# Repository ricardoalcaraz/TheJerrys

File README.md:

# The Jerrys Micromouse Team
*******************************************
Code for solving 16x16 maze using floodfill algorithm on Tensilica architecture.

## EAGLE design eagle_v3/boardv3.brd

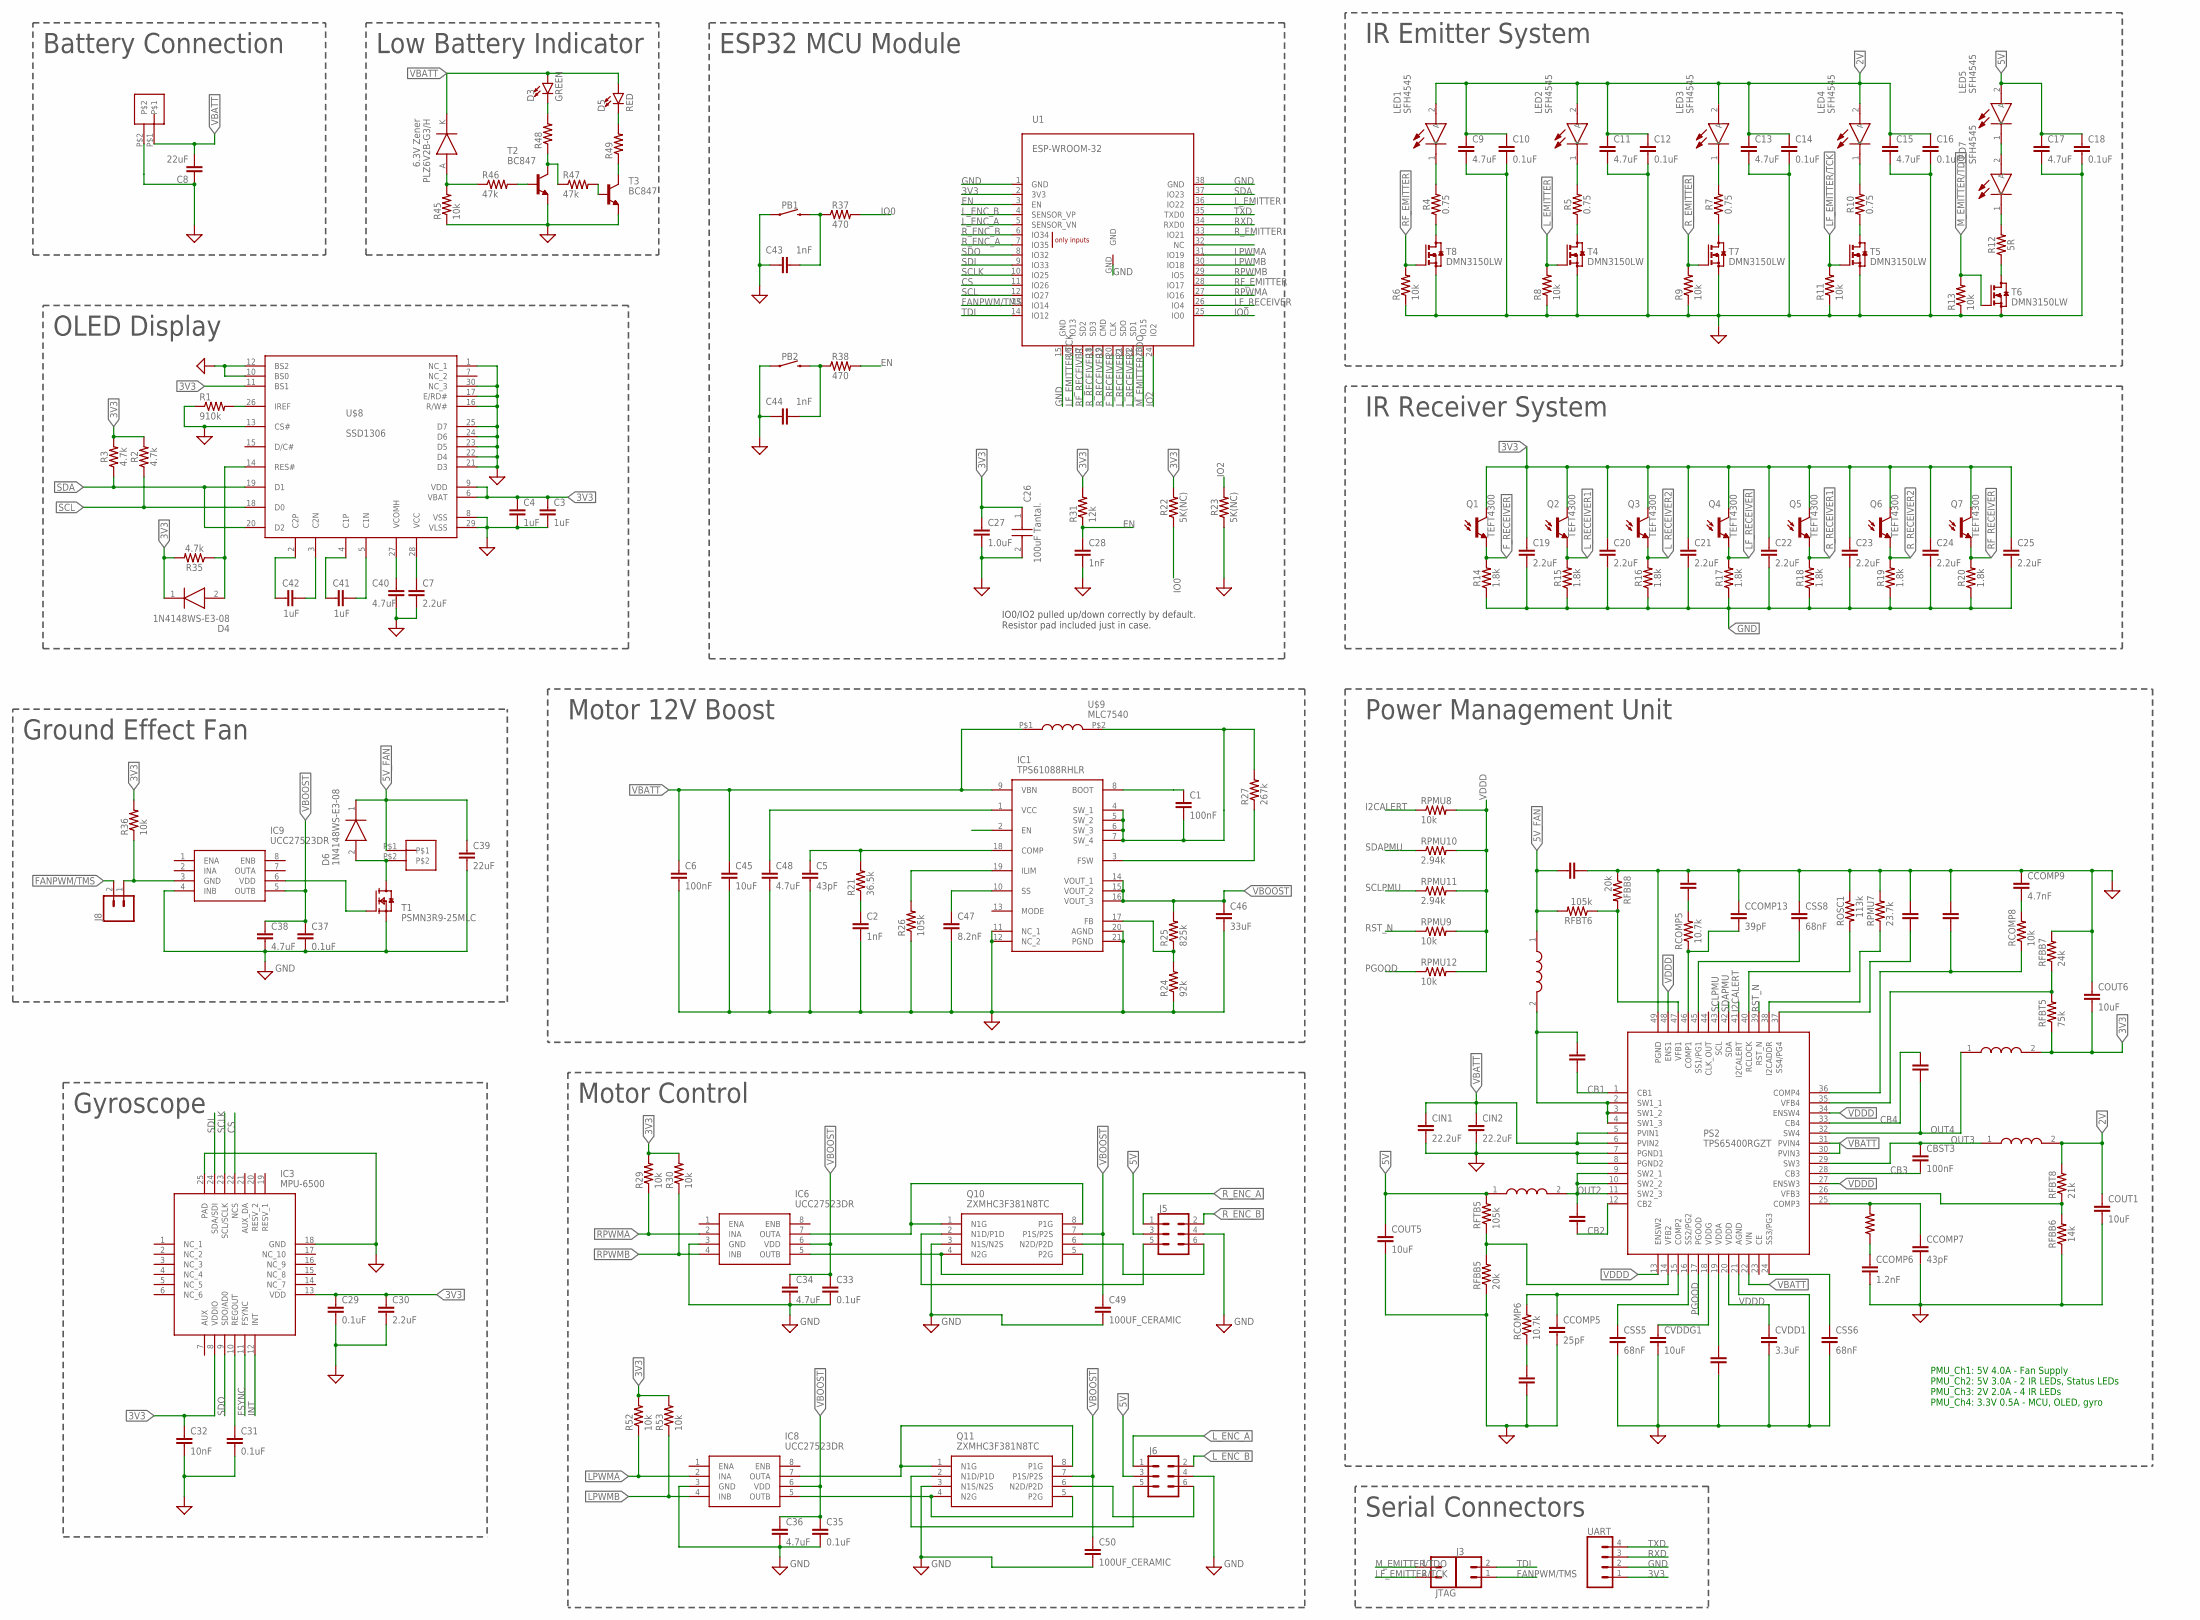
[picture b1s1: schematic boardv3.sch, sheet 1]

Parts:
C1: 100nF; C0402
C2: 1nF; C0805
C3, C4, C41, C42: 1uF; C0402
C5: 43pF; C0402
C6: 100nF; C0805
C7: 2.2uF; C0402
C8, C39: 22uF; 0805
C9, C11, C13, C15, C17, C34, C36, C38: 4.7uF; 0603
C10, C12, C14, C16, C18: 0.1uF; C0402
C19, C20, C21, C22, C23, C24, C25, C30: 2.2uF; 0603
C26: 100uF Tantal.; CAPPM3528X210N
C27: 1.0uF; 0402
C28, C43, C44: 1nF; 0603
C29, C31, C33, C35, C37: 0.1uF; 0603
C32: 10nF; 0603
C40, C48: 4.7uF; C0402
C45: 10uF; C0402
C46: 33uF; C1206
C47: 8.2nF; C0805
C49, C50: 100UF_CERAMIC; C1210
CBST1, CBST2, CBST3, CBST4: 100nF; C0402
CCOMP5: 25pF; C0603
CCOMP6, CCOMP11: 1.2nF; C0603
CCOMP7: 43pF; C0603
CCOMP8: 1.8nF; C0603
CCOMP9: 4.7nF; C0603
CCOMP10: 82pF; C0603
CCOMP13: 39pF; C0603
CIN1, CIN2, CIN3: 22.2uF; 0805
COUT1, COUT5, COUT6: 10uF; C0402
CSS5, CSS6, CSS7, CSS8: 68nF; C0402
CVDD1: 3.3uF; C0402
CVDDA1: 4.7uF; 0603
CVDDG1: 10uF; C0603
D3: GREEN; LED-0603
D4, D6: 1N4148WS-E3-08; SOD2713X115N
D5: RED; LED-0603
IC1: TPS61088RHLR; RHL(R-PVQFN-N20)_1
IC3: MPU-6500; QFN40P300X300X95-25N
IC6, IC8, IC9: UCC27523DR; SOIC127P600X175-8N
J2, J7: 2_PIN_JST-XH
J3, J8: CONN_02; 1X02
J5, J6: CONN_03X22X3_SILK_MALE_PTH; 2X3
JTAG: CONN_02; 1X02
L5: XAL4030-332MEB
L6: SDR0302-100ML; SDR0302-471KL
L7: XAL4030-472MEB; XAL4030-332MEB
L8: XFL4020-472MEB; XFL4020-222ME
LED1, LED2, LED3, LED4, LED5, LED7: SFH4545; SFH_4556P
PB1, PB2: SPST_3X6X2.5MMPB; 3X6X2.5MMSPB
PLZ6V2B-G3/H: 6.3V Zener; DO-219AC
PS2: TPS65400RGZT; QFN50P700X700X100-49N
Q1, Q2, Q3, Q4, Q5, Q6, Q7: TEFT4300
Q10, Q11: ZXMHC3F381N8TC; SOIC127P600X175-8N
R1: 910k; R0402
R2, R3, R35: 4.7k; 0603
R4, R5, R7, R10: 0.75; 0805
R6, R8, R9, R11, R13, R29, R30, R36, R52, R53: 10k; R0201
R12: 5R; 0805
R14, R15, R16, R17, R18, R19, R20: 1.8k; 0603
R21: 36.5k; R0201
R22, R23: 5K(NC); 0402
R24: 92k; R0805
R25: 825k; R0402
R26: 105k; R0201
R27: 267k; R0402
R31: 12k; R0201
R37, R38: 470; 0603
R45: 10k; R0402
R46, R47: 47k; R0402
R48, R49: R-US_R0603; R0603
RCOMP5: 10.7k; 0402
RCOMP6: 10.7k; R0402
RCOMP7: 9.31k; R0402
RCOMP8: 10k; R0201
RFBB5, RFBB8: 20k; R0805
RFBB6: 14k; 0402
RFBB7: 24k; R0805
RFBT5: 75k; R0402
RFBT6: 105k; R0201
RFBT8: 21k; R0402
RFTB5: 105k; R0201
ROSC1: 113k; R0402
RPMU7: 23.7k; R0201
RPMU8, RPMU9, RPMU12: 10k; R0201
RPMU10, RPMU11: 2.94k; R0402
T1: PSMN3R9-25MLC; SOT1210
T2, T3: BC847; SOT23
T4, T5, T6, T7, T8: DMN3150LW; SOT323
U1: ESP-WROOM-32
U$8: SSD1306; 30PINFPC_P0.7MM
U$9: MLC7540
UART: CONN_04; 1X04

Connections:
2V: C9.1, C10.1, C11.1, C12.1, C13.1, C14.1, C15.1, C16.1, COUT1.1, L8.2, LED1.2 (A), LED2.2 (A), LED3.2 (A), LED4.2 (A), RFBT8.2
3V3: C3.1, C4.1, C19.1, C20.1, C21.1, C22.1, C23.1, C24.1, C25.1, C26.1, C27.1, C29.1, C30.1, C32.1, COUT6.2, D4.1 (K), IC3.8 (VDDIO), IC3.13 (VDD), L6.2, Q1.1 (C), Q2.1 (C), Q3.1 (C), Q4.1 (C), Q5.1 (C), Q6.1 (C), Q7.1 (C), R2.2, R3.2, R22.2, R29.2, R30.2, R31.2, R35.2, R36.2, R52.2, R53.2, RFBT5.1, U1.2 (3V3), U$8.6 (VBAT), U$8.9 (VDD), U$8.11 (BS1), UART.1
5V: C17.1, C18.1, COUT5.1, J5.3, J6.3, L5.1, LED5.2 (A), RFTB5.2
5V_FAN: C39.1, CIN3.1, D6.1 (K), J7.P$1, L7.1, RFBT6.2
BOOSTEN: IC1.2 (EN)
CB1: CBST1.1, PS2.1 (CB1)
CB2: CBST2.1, PS2.12 (CB2)
CB3: CBST3.2, PS2.28 (CB3)
CB4: CBST4.2, PS2.33 (CB4)
COMP1: CCOMP13.2, PS2.46 (COMP1), RCOMP5.1
COMP2: CCOMP5.1, PS2.15 (COMP2), RCOMP6.2
COMP3: CCOMP7.1, PS2.25 (COMP3), RCOMP7.2
COMP4: CCOMP10.1, PS2.36 (COMP4), RCOMP8.1
CS: IC3.22 (NCS), U1.11 (IO26)
EN: C28.1, R31.1, R38.2, U1.3 (EN)
FANPWM: IC9.3 (GND), J8.1, R36.1
FANPWM/TMS: J3.1, J8.2, U1.13 (IO14)
FSYNC: IC3.11 (FSYNC)
F_RECEIVER: Q1.2 (E), R14.2, U1.20 (CLK)
GND: C2.2, C3.2, C4.2, C5.2, C6.2, C7.2, C8.1, C9.2, C10.2, C11.2, C12.2, C13.2, C14.2, C15.2, C16.2, C17.2, C18.2, C19.2, C20.2, C21.2, C22.2, C23.2, C24.2, C25.2, C26.2, C27.2, C28.2, C29.2, C30.2, C31.2, C32.2, C33.2, C34.2, C35.2, C36.2, C37.2, C38.2, C39.2, C40.2, C43.1, C44.1, C45.2, C46.2, C47.2, C48.2, C49.2, C50.2, CCOMP5.2, CCOMP6.2, CCOMP7.2, CCOMP8.1, CCOMP9.1, CCOMP10.2, CCOMP11.1, CCOMP13.1, CIN1.2, CIN2.2, CIN3.2, COUT1.2, COUT5.2, COUT6.1, CSS5.2, CSS6.2, CSS7.2, CSS8.1, CVDD1.2, CVDDA1.1, CVDDG1.2, IC1.11 (NC_1), IC1.12 (NC_2), IC1.20 (AGND), IC1.21 (PGND), IC3.18 (GND), IC3.25 (PAD), IC6.3 (GND), IC8.3 (GND), IC9.4 (INB), J2.P$2, J5.4, J6.4, PB1.1, PB2.1, PS2.7 (PGND1), PS2.8 (PGND2), PS2.21 (AGND), PS2.49 (PGND), Q10.3 (N1S/N2S), Q11.3 (N1S/N2S), R1.1, R6.1, R8.1, R9.1, R11.1, R13.1, R14.1, R15.1, R16.1, R17.1, R18.1, R19.1, R20.1, R23.1, R24.1, R26.1, R45.1, RFBB5.1, RFBB6.1, RFBB7.2, RFBB8.1, ROSC1.1, RPMU7.2, T1.1 (S), T1.2 (S), T1.3 (S), T2.2 (E), T3.2 (E), T4.S, T5.S, T6.S, T7.S, T8.S, U1.1 (GND), U1.15 (GND), U1.38 (GND), U1.GND, U$8.1 (NC_1), U$8.8 (VSS), U$8.10 (BS0), U$8.12 (BS2), U$8.13 (CS#), U$8.16 (R/W#), U$8.17 (E/RD#), U$8.21 (D3), U$8.22 (D4), U$8.23 (D5), U$8.24 (D6), U$8.25 (D7), U$8.29 (VLSS), U$8.30 (NC_3), UART.2
I2CADDR: PS2.38 (I2CADDR), RPMU7.1
I2CALERT: PS2.41 (I2CALERT), RPMU8.1
INT: IC3.12 (INT)
IO0: R22.1, R37.2, U1.25 (IO0)
IO2: R23.2, U1.24 (IO2)
LF_EMITTER/TCK: JTAG.2, R11.2, T5.G, U1.16 (IO13)
LF_RECEIVER: Q4.2 (E), R17.2, U1.26 (IO4)
LPWMA: IC8.2 (INA), R52.1, U1.31 (IO19)
LPWMB: IC8.4 (INB), R53.1, U1.30 (IO18)
L_EMITTER: R8.2, T4.G, U1.36 (IO22)
L_ENC_A: J6.1, U1.5 (SENSOR_VN)
L_ENC_B: J6.2, U1.4 (SENSOR_VP)
L_RECEIVER1: Q2.2 (E), R15.2, U1.22 (SD1)
L_RECEIVER2: Q3.2 (E), R16.2, U1.21 (SDO)
M_EMITTER/TDO: JTAG.1, R13.2, T6.G, U1.23 (IO15)
N1D: J5.5, Q10.2 (N1D/P1D)
N1D_2: J6.5, Q11.2 (N1D/P1D)
N1G: IC6.7 (OUTA), Q10.1 (N1G), Q10.8 (P1G)
N1G_2: IC8.7 (OUTA), Q11.1 (N1G), Q11.8 (P1G)
N2D: J5.6, Q10.6 (N2D/P2D)
N2D_2: J6.6, Q11.6 (N2D/P2D)
N2G: IC6.5 (OUTB), Q10.4 (N2G), Q10.5 (P2G)
N2G_2: IC8.5 (OUTB), Q11.4 (N2G), Q11.5 (P2G)
unnamed: C5.1, IC1.18 (COMP), R21.2
unnamed: C1.1, IC1.8 (BOOT)
unnamed: C1.2, IC1.4 (SW_1), IC1.5 (SW_2), IC1.6 (SW_3), IC1.7 (SW_4), R27.2, U$9.P$2 (2)
unnamed: C48.1, IC1.1 (VCC)
unnamed: C47.1, IC1.10 (SS)
unnamed: R46.2, T2.1 (B)
unnamed: LED5.1 (K), LED7.2 (A)
unnamed: IC1.19 (ILIM), R26.2
unnamed: C2.1, R21.1
unnamed: LED1.1 (K), R4.2
unnamed: R4.1, T8.D
unnamed: LED7.1 (K), R12.2
unnamed: LED2.1 (K), R5.2
unnamed: R5.1, T4.D
unnamed: R12.1, T6.D
unnamed: C43.2, PB1.2, R37.1
unnamed: LED3.1 (K), R7.2
unnamed: R7.1, T7.D
unnamed: IC9.6 (VDD), T1.4 (G)
unnamed: IC1.17 (FB), R24.2, R25.1
unnamed: D6.2 (A), J7.P$2, T1.MB (D)
unnamed: LED4.1 (K), R10.2
unnamed: R10.1, T5.D
unnamed: IC1.3 (FSW), R27.1
unnamed: C44.2, PB2.2, R38.1
unnamed: PLZ6V2B-G3/H.A, R45.2, R46.1
unnamed: R47.1, R48.1, T2.3 (C)
unnamed: R47.2, T3.1 (B)
unnamed: D3.C, R48.2
unnamed: C42.1, U$8.2 (C2P)
unnamed: D5.C, R49.2
unnamed: R49.1, T3.3 (C)
unnamed: C42.2, U$8.3 (C2N)
unnamed: C41.1, U$8.4 (C1P)
unnamed: C41.2, U$8.5 (C1N)
unnamed: C40.1, U$8.27 (VCOMH)
unnamed: C7.1, U$8.28 (VCC)
unnamed: D4.2 (A), R35.1, U$8.14 (RES#)
unnamed: R1.2, U$8.26 (IREF)
unnamed: CCOMP6.1, RCOMP7.1
unnamed: CCOMP8.2, RCOMP6.1
unnamed: CCOMP9.2, RCOMP8.2
unnamed: CCOMP11.2, RCOMP5.2
NC: U1.32 (NC)
OUT1: CBST1.2, L7.2, PS2.2 (SW1_1), PS2.3 (SW1_2), PS2.4 (SW1_3)
OUT2: CBST2.2, L5.2, PS2.9 (SW2_1), PS2.10 (SW2_2), PS2.11 (SW2_3)
OUT3: CBST3.1, L8.1, PS2.29 (SW3)
OUT4: CBST4.1, L6.1, PS2.32 (SW4)
PGOOD: PS2.17 (PGOOD), RPMU12.1
RCLOCK: PS2.40 (RCLOCK), ROSC1.2
REGOUT: C31.1, IC3.10 (REGOUT)
RF_EMITTER: R6.2, T8.G, U1.28 (IO17)
RF_RECEIVER: Q7.2 (E), R20.2, U1.17 (SD2)
RPWMA: IC6.2 (INA), R29.1, U1.27 (IO16)
RPWMB: IC6.4 (INB), R30.1, U1.29 (IO5)
RST_N: PS2.39 (RST_N), RPMU9.1
RXD: U1.34 (RXD0), UART.3
R_EMITTER: R9.2, T7.G, U1.33 (IO21)
R_ENC_A: J5.1, U1.7 (IO35)
R_ENC_B: J5.2, U1.6 (IO34)
R_RECEIVER1: Q5.2 (E), R18.2, U1.18 (SD3)
R_RECEIVER2: Q6.2 (E), R19.2, U1.19 (CMD)
SCL: R2.1, U1.12 (IO27), U$8.18 (D0)
SCLK: IC3.23 (SCL/SCLK), U1.10 (IO25)
SCLPMU: PS2.43 (SCL), RPMU11.1
SDA: R3.1, U1.37 (IO23), U$8.19 (D1), U$8.20 (D2)
SDAPMU: PS2.42 (SDA), RPMU10.1
SDI: IC3.24 (SDA/SDI), U1.9 (IO33)
SDO: IC3.9 (SDO/AD0), U1.8 (IO32)
SS1: CSS8.2, PS2.45 (SS1/PG1)
SS2: CSS5.1, PS2.16 (SS2/PG2)
SS3: CSS6.1, PS2.24 (SS3/PG3)
SS4: CSS7.1, PS2.37 (SS4/PG4)
TDI: J3.2, U1.14 (IO12)
TXD: U1.35 (TXD0), UART.4
VBATT: C6.1, C8.2, C45.1, CIN1.1, CIN2.1, D3.A, D5.A, IC1.9 (VBN), J2.P$1, PLZ6V2B-G3/H.K, PS2.5 (PVIN1), PS2.6 (PVIN2), PS2.22 (VIN), PS2.30 (PVIN3), PS2.31 (PVIN4), U$9.P$1 (1)
VBOOST: C33.1, C34.1, C35.1, C36.1, C37.1, C38.1, C46.1, C49.1, C50.1, IC1.14 (VOUT_1), IC1.15 (VOUT_2), IC1.16 (VOUT_3), IC6.6 (VDD), IC8.6 (VDD), IC9.5 (OUTB), Q10.7 (P1S/P2S), Q11.7 (P1S/P2S), R25.2
VDDA: CVDDA1.2, PS2.19 (VDDA)
VDDD: CVDD1.1, PS2.13 (ENSW2), PS2.20 (VDDD), PS2.27 (ENSW3), PS2.34 (ENSW4), PS2.48 (ENS1), RPMU8.2, RPMU9.2, RPMU10.2, RPMU11.2, RPMU12.2
VDDG: CVDDG1.1, PS2.18 (VDDG)
VFB1: PS2.47 (VFB1), RFBB8.2, RFBT6.1
VFB2: PS2.14 (VFB2), RFBB5.2, RFTB5.1
VFB3: PS2.26 (VFB3), RFBB6.2, RFBT8.1
VFB4: PS2.35 (VFB4), RFBB7.1, RFBT5.2

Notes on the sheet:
IR Emitter System
IR Receiver System
IO0/IO2 pulled up/down correctly by default. Resistor pad included just in case.
ESP32 MCU Module
Serial Connectors
Gyroscope
Motor Control
Ground Effect Fan
OLED Display
Battery Connection
Motor 12V Boost
Low Battery Indicator
Power Management Unit
PMU_Ch1: 5V 4.0A - Fan Supply PMU_Ch2: 5V 3.0A - 2 IR LEDs, Status LEDs PMU_Ch3: 2V 2.0A - 4 IR LEDs PMU_Ch4: 3.3V 0.5A - MCU, OLED, gyro

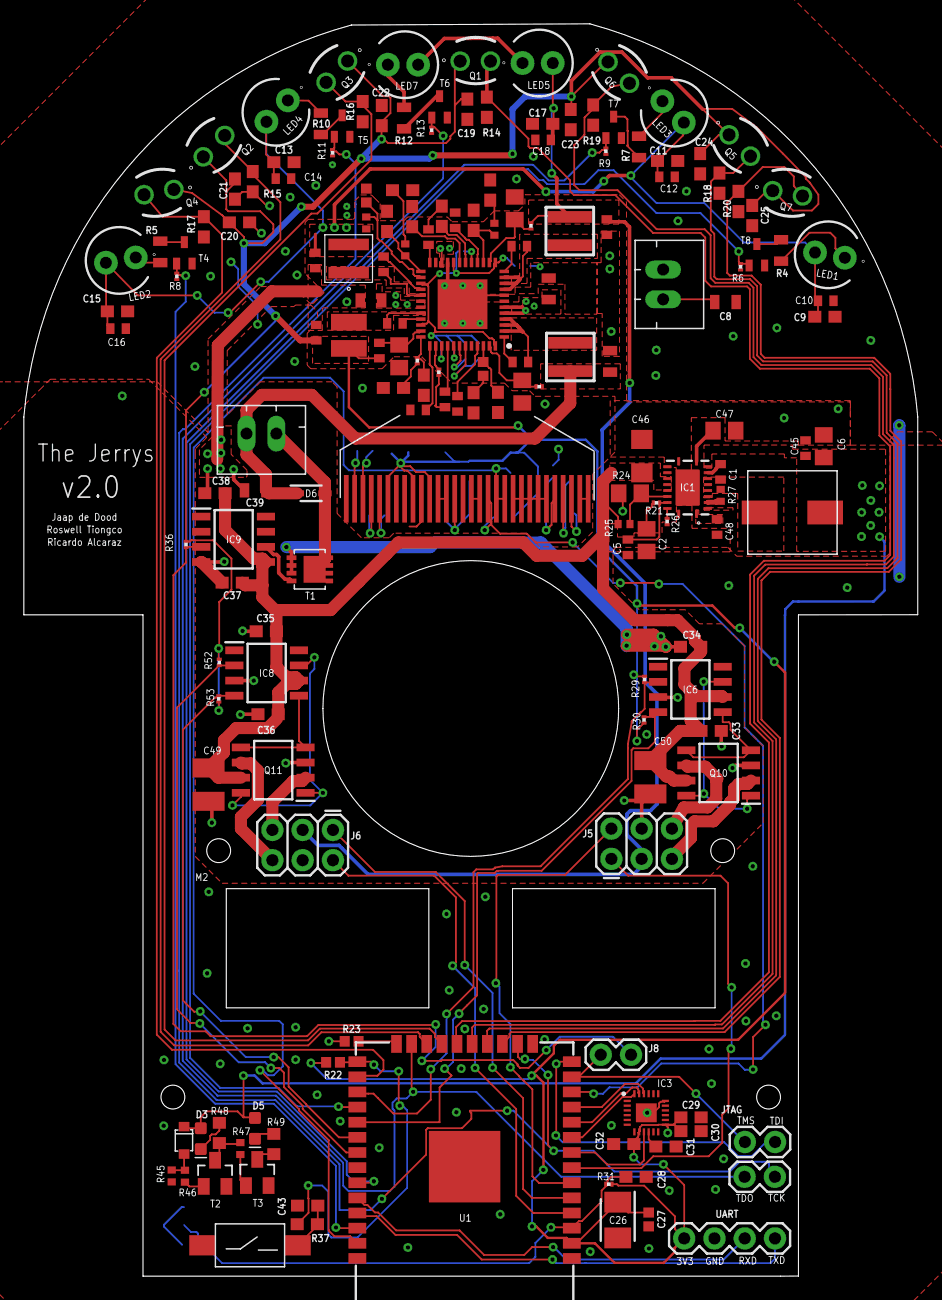
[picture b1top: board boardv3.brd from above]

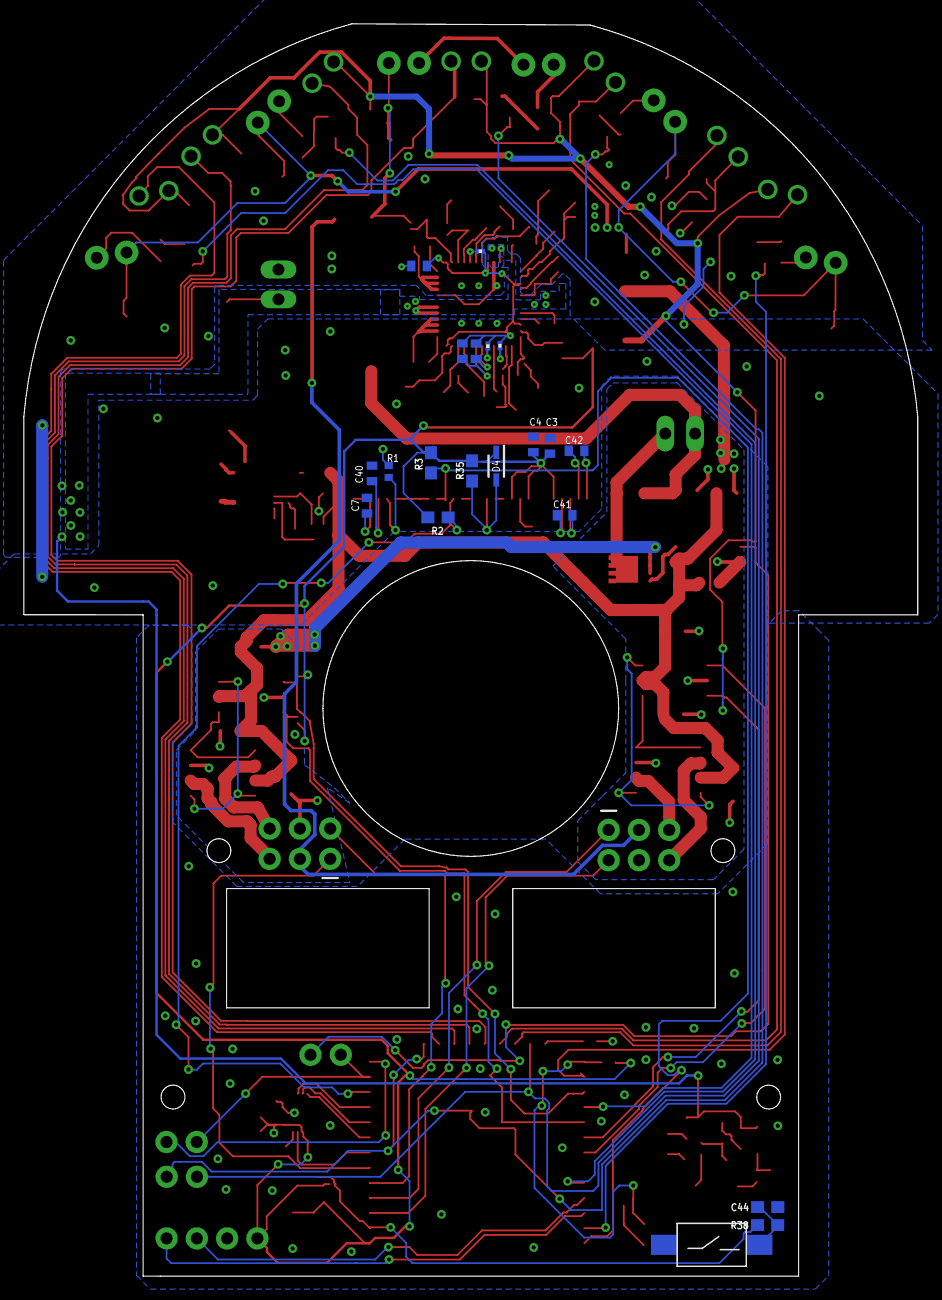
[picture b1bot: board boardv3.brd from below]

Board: 2 copper layers, 75.0 x 105.1 mm, 186 parts (20 on the bottom side), 123 nets.

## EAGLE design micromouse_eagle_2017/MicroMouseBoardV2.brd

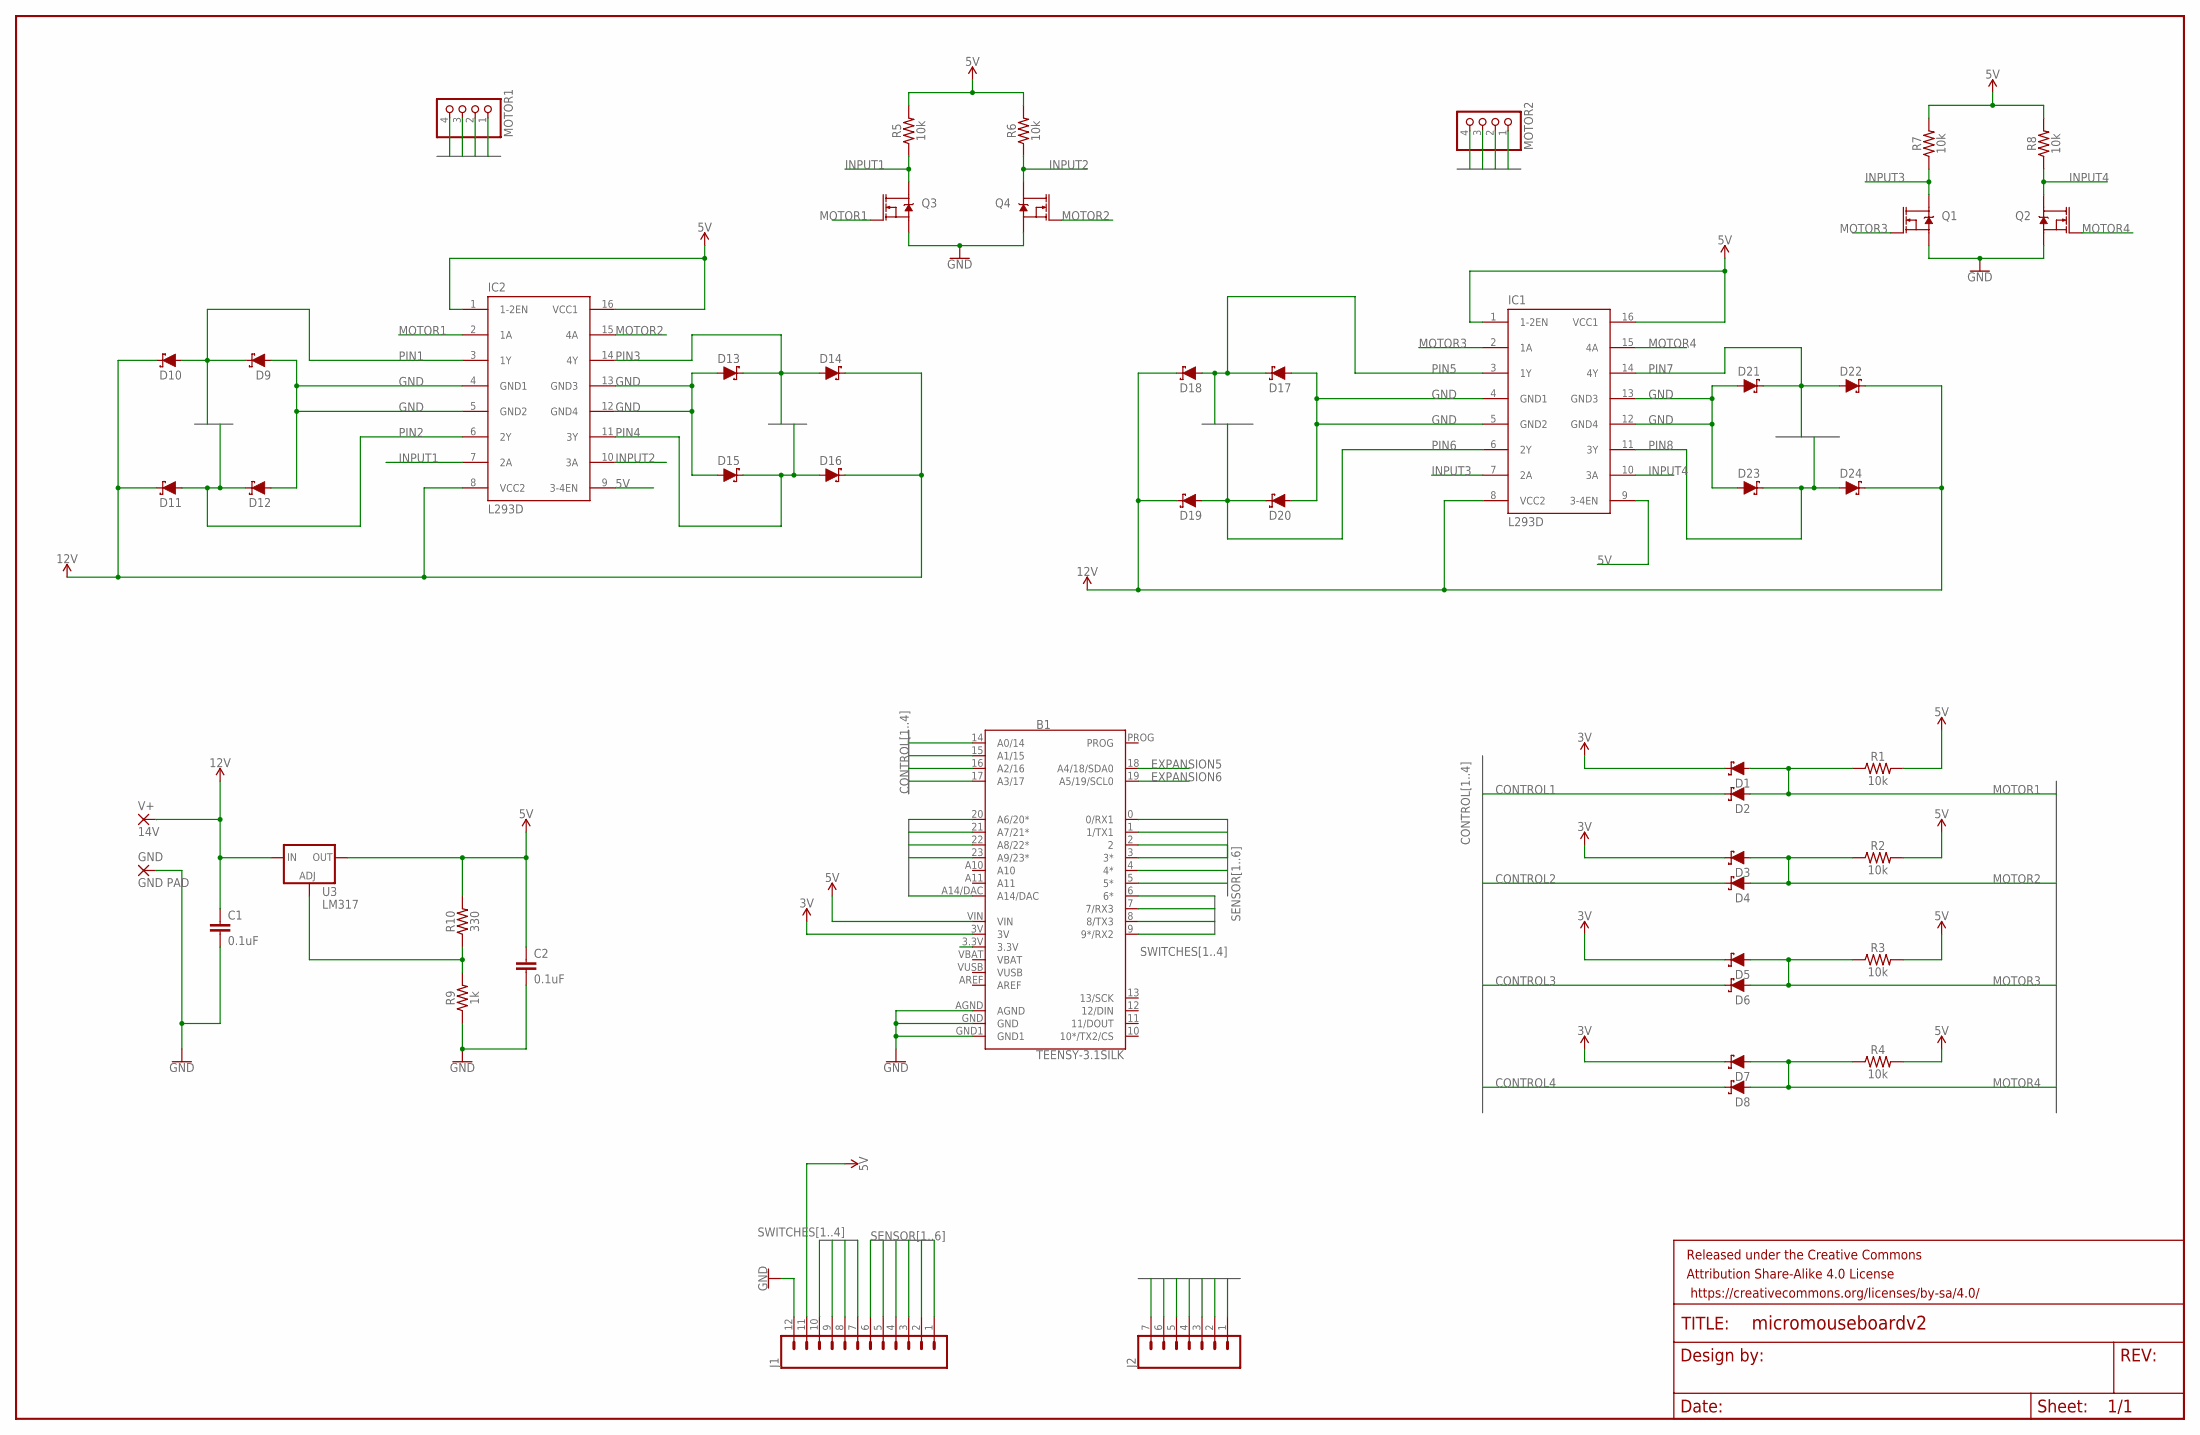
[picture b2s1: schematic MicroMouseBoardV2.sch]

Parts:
B1: TEENSY-3.1SILK; TEENSY-3.1
C1, C2: 0.1uF; 0603
D1, D2, D3, D4, D5, D6, D7, D8, D9, D10, D11, D12, D13, D14, D15, D16, D17, D18, D19, D20, D21, D22, D23, D24: DIODE-SCHOTTKY-PMEG4005EJ; SOD-323
FRAME1: FRAME-LEDGER; CREATIVE_COMMONS
GND: GND PAD; SMD2,54-5,08
IC1, IC2: L293D; DIL16
J1: CONN_12; 1X12
J2: CONN_07LOCK; 1X07_LOCK
MOTOR1, MOTOR2: PINHD-1X4; 1X04
Q1, Q2, Q3, Q4: MOSFET-NCH-2N7002PW; SOT323
R1, R2, R3, R4, R5, R6, R7, R8: 10k; 0603
R9: 1k; 0603
R10: 330; 0603
U3: LM317; TO220-ADJ
V+: 14V; SMD2,54-5,08

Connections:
3.3V: B1.3V, D1.C, D3.C, D5.C, D7.C
5V: B1.VIN, C2.1, IC1.1 (1-2EN), IC1.9 (3-4EN), IC1.16 (VCC1), IC2.1 (1-2EN), IC2.9 (3-4EN), IC2.16 (VCC1), J1.11, R1.2, R2.2, R3.2, R4.2, R5.2, R6.2, R7.2, R8.2, R10.2, U3.OUT
12V: C1.1, D10.C, D11.C, D14.C, D16.C, D18.C, D19.C, D22.C, D24.C, IC1.8 (VCC2), IC2.8 (VCC2), U3.IN, V+.1
CONTROL1: B1.17 (A3/17), D2.C
CONTROL2: B1.16 (A2/16), D4.C
CONTROL3: B1.15 (A1/15), D6.C
CONTROL4: B1.14 (A0/14), D8.C
EXPANSION1: B1.20 (A6/20*), J2.1
EXPANSION2: B1.21 (A7/21*), J2.2
EXPANSION3: B1.22 (A8/22*), J2.3
EXPANSION4: B1.23 (A9/23*), J2.4
EXPANSION5: B1.18 (A4/18/SDA0), J2.5
EXPANSION6: B1.19 (A5/19/SCL0), J2.6
EXPANSION7: B1.A14/DAC, J2.7
GND: B1.AGND, B1.GND, B1.GND1, C1.2, C2.2, D9.A, D12.A, D13.A, D15.A, D17.A, D20.A, D21.A, D23.A, GND.1, IC1.4 (GND1), IC1.5 (GND2), IC1.12 (GND4), IC1.13 (GND3), IC2.4 (GND1), IC2.5 (GND2), IC2.12 (GND4), IC2.13 (GND3), J1.12, Q1.2 (S), Q2.2 (S), Q3.2 (S), Q4.2 (S), R9.1
INPUT1: IC2.7 (2A), Q3.3 (D), R5.1
INPUT2: IC2.10 (3A), Q4.3 (D), R6.1
INPUT3: IC1.7 (2A), Q1.3 (D), R7.1
INPUT4: IC1.10 (3A), Q2.3 (D), R8.1
MOTOR1: D1.A, D2.A, IC2.2 (1A), Q3.1 (G), R1.1
MOTOR2: D3.A, D4.A, IC2.15 (4A), Q4.1 (G), R2.1
MOTOR3: D5.A, D6.A, IC1.2 (1A), Q1.1 (G), R3.1
MOTOR4: D7.A, D8.A, IC1.15 (4A), Q2.1 (G), R4.1
unnamed: R9.2, R10.1, U3.ADJ
PIN1: D9.C, D10.A, IC2.3 (1Y), MOTOR1.4
PIN2: D11.A, D12.C, IC2.6 (2Y), MOTOR1.3
PIN3: D13.C, D14.A, IC2.14 (4Y), MOTOR1.2
PIN4: D15.C, D16.A, IC2.11 (3Y), MOTOR1.1
PIN5: D17.C, D18.A, IC1.3 (1Y), MOTOR2.4
PIN6: D19.A, D20.C, IC1.6 (2Y), MOTOR2.3
PIN7: D21.C, D22.A, IC1.14 (4Y), MOTOR2.2
PIN8: D23.C, D24.A, IC1.11 (3Y), MOTOR2.1
SENSOR1: B1.0 (0/RX1), J1.1
SENSOR2: B1.1 (1/TX1), J1.2
SENSOR3: B1.2, J1.3
SENSOR4: B1.3 (3*), J1.4
SENSOR5: B1.4 (4*), J1.5
SENSOR6: B1.5 (5*), J1.6
SWITCHES1: B1.6 (6*), J1.7
SWITCHES2: B1.7 (7/RX3), J1.8
SWITCHES3: B1.8 (8/TX3), J1.9
SWITCHES4: B1.9 (9*/RX2), J1.10
VBAT: B1.VBAT
VUSB: B1.VUSB

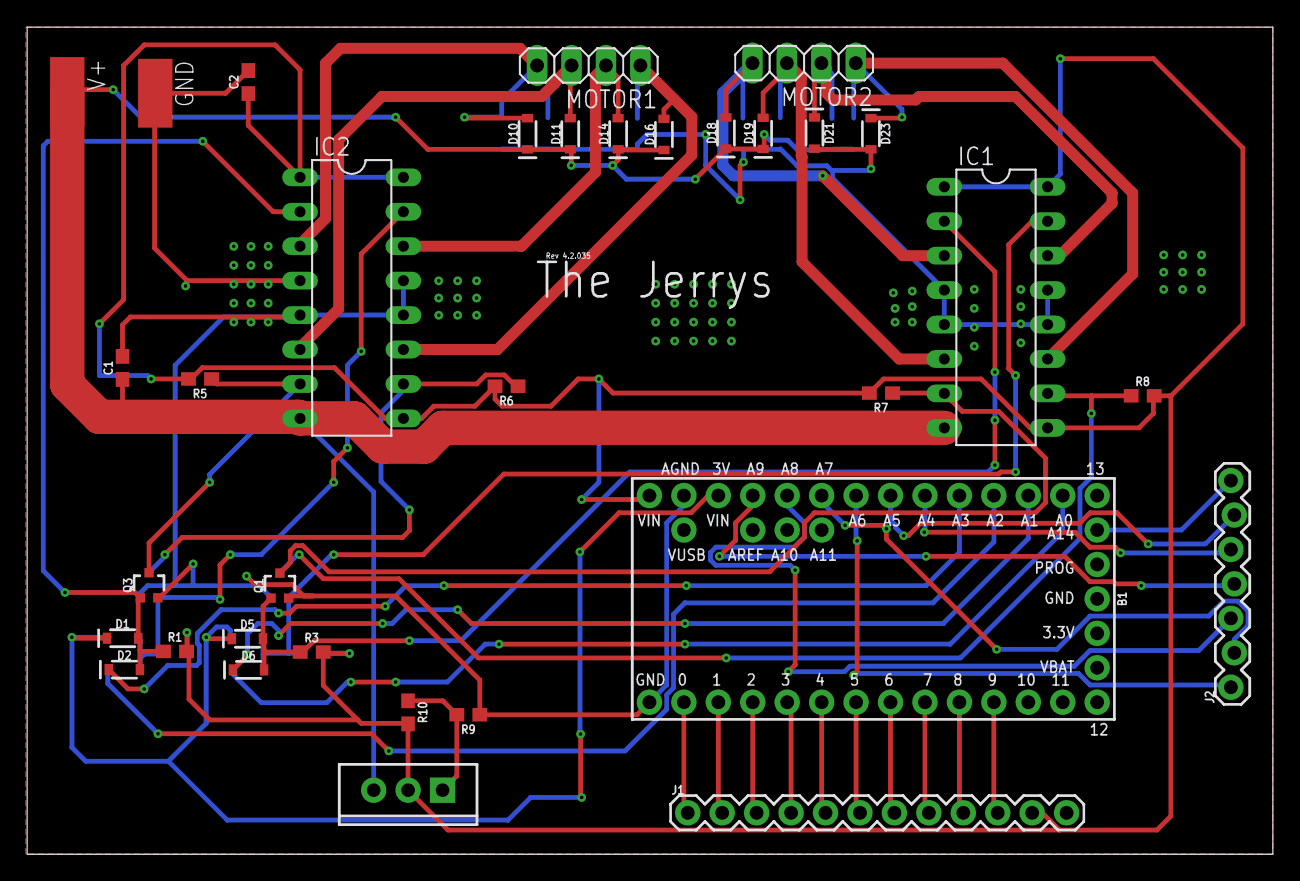
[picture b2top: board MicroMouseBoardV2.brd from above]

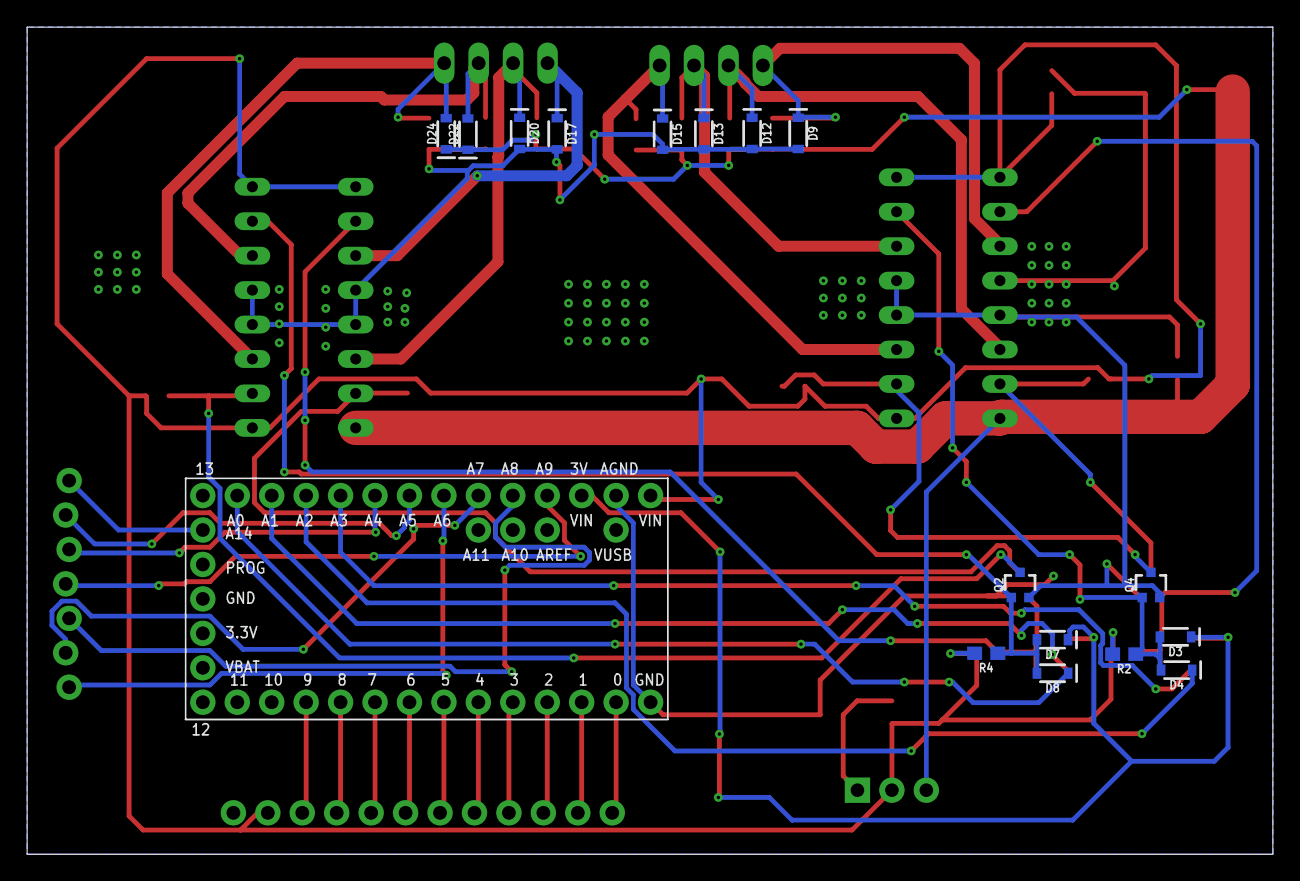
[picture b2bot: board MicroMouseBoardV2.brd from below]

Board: 2 copper layers, 91.9 x 61.0 mm, 51 parts (16 on the bottom side), 42 nets.

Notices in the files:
parts and their libraries:
SparkFun-Boards: Licensing: Creative Commons ShareAlike 4.0 International - https://creativecommons.org/licenses/by-sa/4.0
SparkFun-Aesthetics: Released under the Creative Commons Attribution Share-Alike 4.0 License
SparkFun-Aesthetics: https://creativecommons.org/licenses/by-sa/4.0
